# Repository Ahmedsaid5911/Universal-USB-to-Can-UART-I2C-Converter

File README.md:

# Universal USB to CAN/UART/I2C Converter
A flexible and reliable USB converter for embedded system developers. This tool allows communication between a host PC and embedded devices via CAN, UART, and I2C protocols using a single USB interface.

## 🔧 Features
USB to CAN communication using CAN transceiver (e.g., MCP2551 or TJA1050)

USB to UART interface (up to 2 UART ports)

USB to I2C interface with master mode support

Cross-platform serial communication via USB CDC

Selectable interface via command or GUI tool

Open-source firmware and host-side tools

## 🧩 Applications
Debugging embedded devices

Communicating with automotive ECUs (CAN)

I2C device testing (sensors, EEPROMs, etc.)

Serial monitoring and control via UART

## 🖼️ Device Preview

The image below shows the USB to CAN/UART/I2C Converter mounted on a breadboard.  
You can see the USB-C connector on the left, the CAN interface on the right (blue connector), and clearly labeled headers for UART, I2C, and power in the center.  
This visual demonstrates the compact and practical layout, ideal for prototyping and embedded system development.

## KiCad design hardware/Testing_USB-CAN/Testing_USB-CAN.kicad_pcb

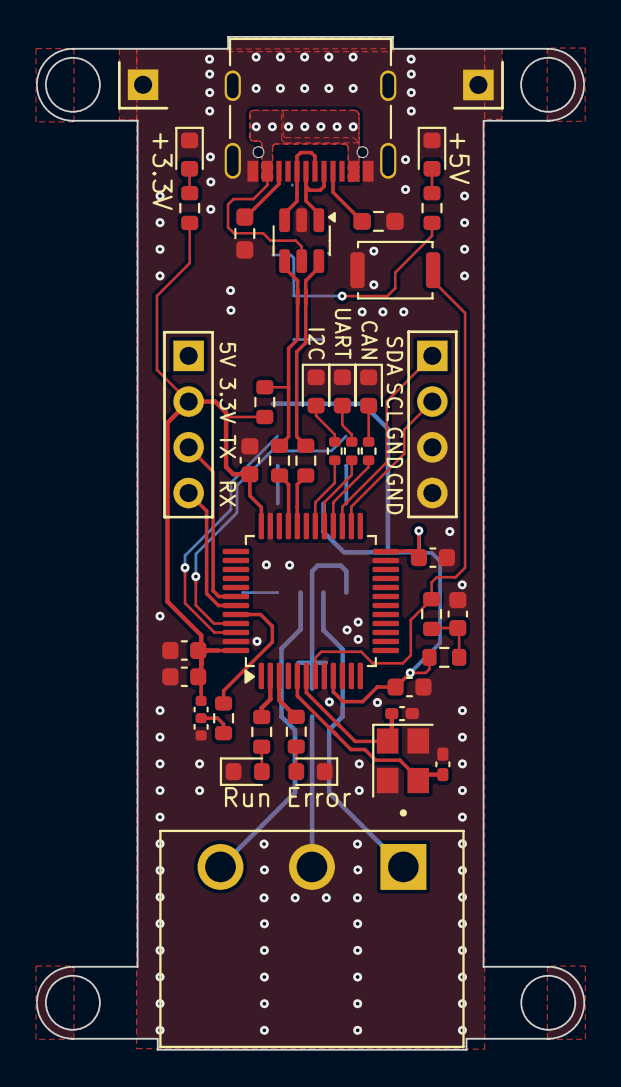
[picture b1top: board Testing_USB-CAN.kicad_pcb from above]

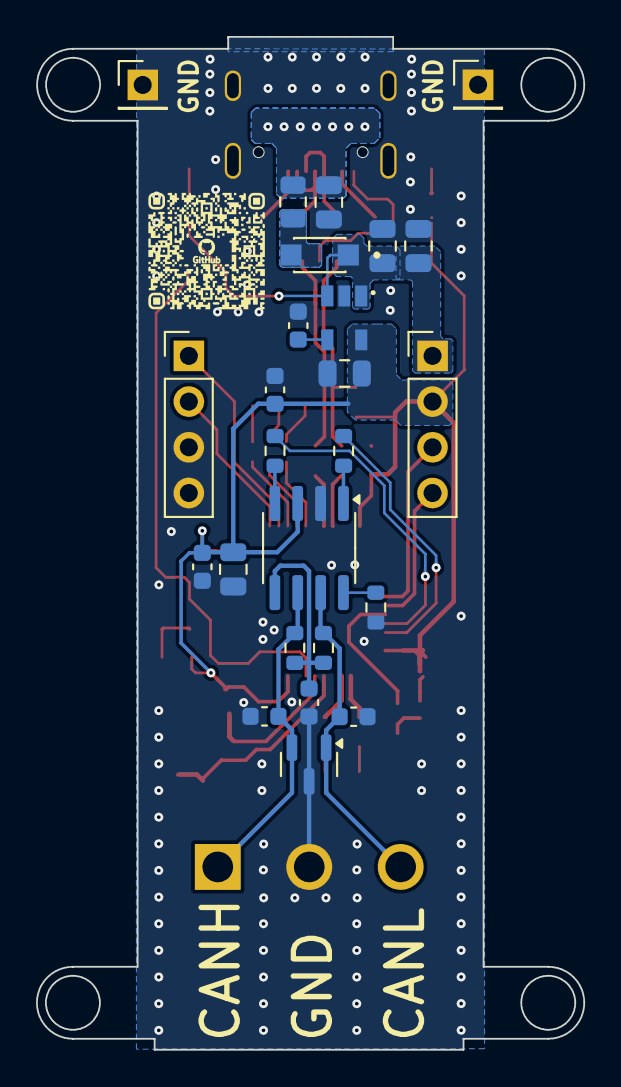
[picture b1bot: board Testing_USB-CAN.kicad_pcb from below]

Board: 4 copper layers, 30.4 x 56.3 mm, 62 parts (25 on the bottom side), 44 nets.

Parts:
C1, C2: 1uf; C_0805_2012Metric
C3, C7: 10uf; C_0805_2012Metric
C4, C14, C15, C16, C17, C18: 100nf; C_0603_1608Metric
C5: 100nf; C_0805_2012Metric
C6: 22pf; C_0603_1608Metric
C9, C10, C11: 30pf; C_0603_1608Metric
C12: 10uf; C_0603_1608Metric
C13: 1uf; C_0603_1608Metric
C19, C20: 20pf; C_0402_1005Metric_Pad0.74x0.62mm_HandSolder
D1: SM712_SOT23; SOT-23
D2, D4, D5, D6, D7, D8, D9: LED; LED_0603_1608Metric
D3: D_Schottky; SODFL3719X135N
F1: Polyfuse_Small; Fuse_0805_2012Metric
J1: USB_C_Receptacle_USB2.0_16P; USB_C_Receptacle_Palconn_UTC16-G
J2: Screw_Terminal_01x03; TerminalBlock
J3, J4: Conn_01x04_Pin; PinHeader_1x04_P2.54mm_Vertical
J5, J6: Conn_01x01_Socket; PinHeader_1x01_P2.54mm_Vertical
J7: Conn_01x03_Pin; BOOT
R1, R2, R3, R9, R12, R13: 1k; R_0603_1608Metric
R4, R19, R21: 10k; R_0603_1608Metric
R5, R6: 5.1k; R_0603_1608Metric_Pad0.98x0.95mm_HandSolder
R7, R8: 60; R_0603_1608Metric
R14, R15, R23: 1k; R_0402_1005Metric
R16, R17: 22; R_0603_1608Metric
R18: 1.5k; R_0603_1608Metric
R20: 120; R_0603_1608Metric
SW1: SW_Push; SW_Push_SPST_NO_Alps_SKRK
U1: RT9193-33GB; SOT94P279X129-5N
U2: SN65HVD230; SOIC-8_3.9x4.9mm_P1.27mm
U3: USBLC6-2SC6; SOT-23-6
U4: STM32F072C8Tx; LQFP-48_7x7mm_P0.5mm
Y1: Crystal_GND24; Crystal_SMD_3225-4Pin_3.2x2.5mm

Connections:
+3.3V: C1.1, C4.1, C7.1, C12.1, C13.1, C14.1, C15.1, C16.1, C17.1, J4.2, J7.1, R9.1, R18.1, R19.1, U1.5 (VOUT), U2.3 (VCC), U4.9 (VDDA), U4.24 (VDD), U4.36 (VDDIO2), U4.48 (VDD)
+5V: C3.1, C5.1, D3.C (K), J4.1, R1.1, U1.1 (VIN), U1.3 (EN)
/B: R15.1, U4.29 (PA8)
/BOOT0: R21.2, U4.44 (BOOT0)
/CAN_N: C11.1, D1.2 (A2), J2.1, R8.2, U2.6 (CANL)
/CAN_P: C10.1, D1.1 (A1), J2.3, R7.1, U2.7 (CANH)
/D0_N: R16.1, U3.6 (I/O1)
/D0_P: R17.1, R18.2, U3.4 (I/O2)
/D_N: J1.A7 (D-), J1.B7 (D-), U3.1 (I/O1)
/D_P: J1.A6 (D+), J1.B6 (D+), U3.3 (I/O2)
/Error: R12.1, U4.3 (PC14)
/G: R14.1, U4.28 (PB15)
/NRST: R20.1, SW1.1, U4.7 (NRST)
/OSC_N: C19.2, U4.5 (PF0), Y1.3
/OSC_P: C20.2, U4.6 (PF1), Y1.1
/R: R23.1, U4.30 (PA9)
/Run: R13.1, U4.2 (PC13)
/Rx: R3.2, U4.45 (PB8)
/SCL: J3.2, U4.26 (PB13)
/SDA: J3.1, U4.27 (PB14)
/Tx: R2.2, U4.46 (PB9)
/UART_RX: J4.4, U4.43 (PB7)
/UART_TX: J4.3, U4.42 (PB6)
/Vref: C9.1, R7.2, R8.1, U2.5 (Vref)
GND: C1.2, C2.2, C3.2, C4.2, C5.2, C6.2, C7.2, C9.2, C10.2, C11.2, C12.2, C13.2, C14.2, C15.2, C16.2, C17.2, C18.2, C19.1, C20.1, D1.3 (common), D2.1 (K), D4.1 (K), D5.1 (K), D6.1 (K), D7.1 (K), D8.1 (K), D9.1 (K), J1.A1 (GND), J1.A12 (GND), J1.B1 (GND), J1.B12 (GND), J1.S1 (SHIELD), J2.2, J3.3, J3.4, J5.1, J6.1, J7.3, R4.2, R5.2, R6.2, SW1.2, U1.2 (GND), U2.2 (GND), U3.2 (GND), U4.8 (VSSA), U4.23 (VSS), U4.35 (VSS), U4.47 (VSS), Y1.2, Y1.4
unnamed: C18.1, R19.2, R20.2
unnamed: D2.2 (A), R1.2
unnamed: D3.A, F1.2
unnamed: D4.2 (A), R9.2
unnamed: D5.2 (A), R12.2
unnamed: D6.2 (A), R13.2
unnamed: D7.2 (A), R14.2
unnamed: D8.2 (A), R15.2
unnamed: D9.2 (A), R23.2
unnamed: J1.A5 (CC1), R5.1
unnamed: J1.B5 (CC2), R6.1
unnamed: J7.2, R21.1
unnamed: C6.1, U1.4 (BP)
unnamed: R2.1, U2.1 (D)
unnamed: R3.1, U2.4 (R)
unnamed: R4.1, U2.8 (Rs)
unnamed: R16.2, U4.32 (PA11)
unnamed: R17.2, U4.33 (PA12)
VDD: C2.1, F1.1, J1.A4 (VBUS), J1.A9 (VBUS), J1.B4 (VBUS), J1.B9 (VBUS), U3.5 (VBUS)

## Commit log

2025-05-14 push all file
2025-05-14 Rename Breadboard v40.png to Breadboard_v40.png
